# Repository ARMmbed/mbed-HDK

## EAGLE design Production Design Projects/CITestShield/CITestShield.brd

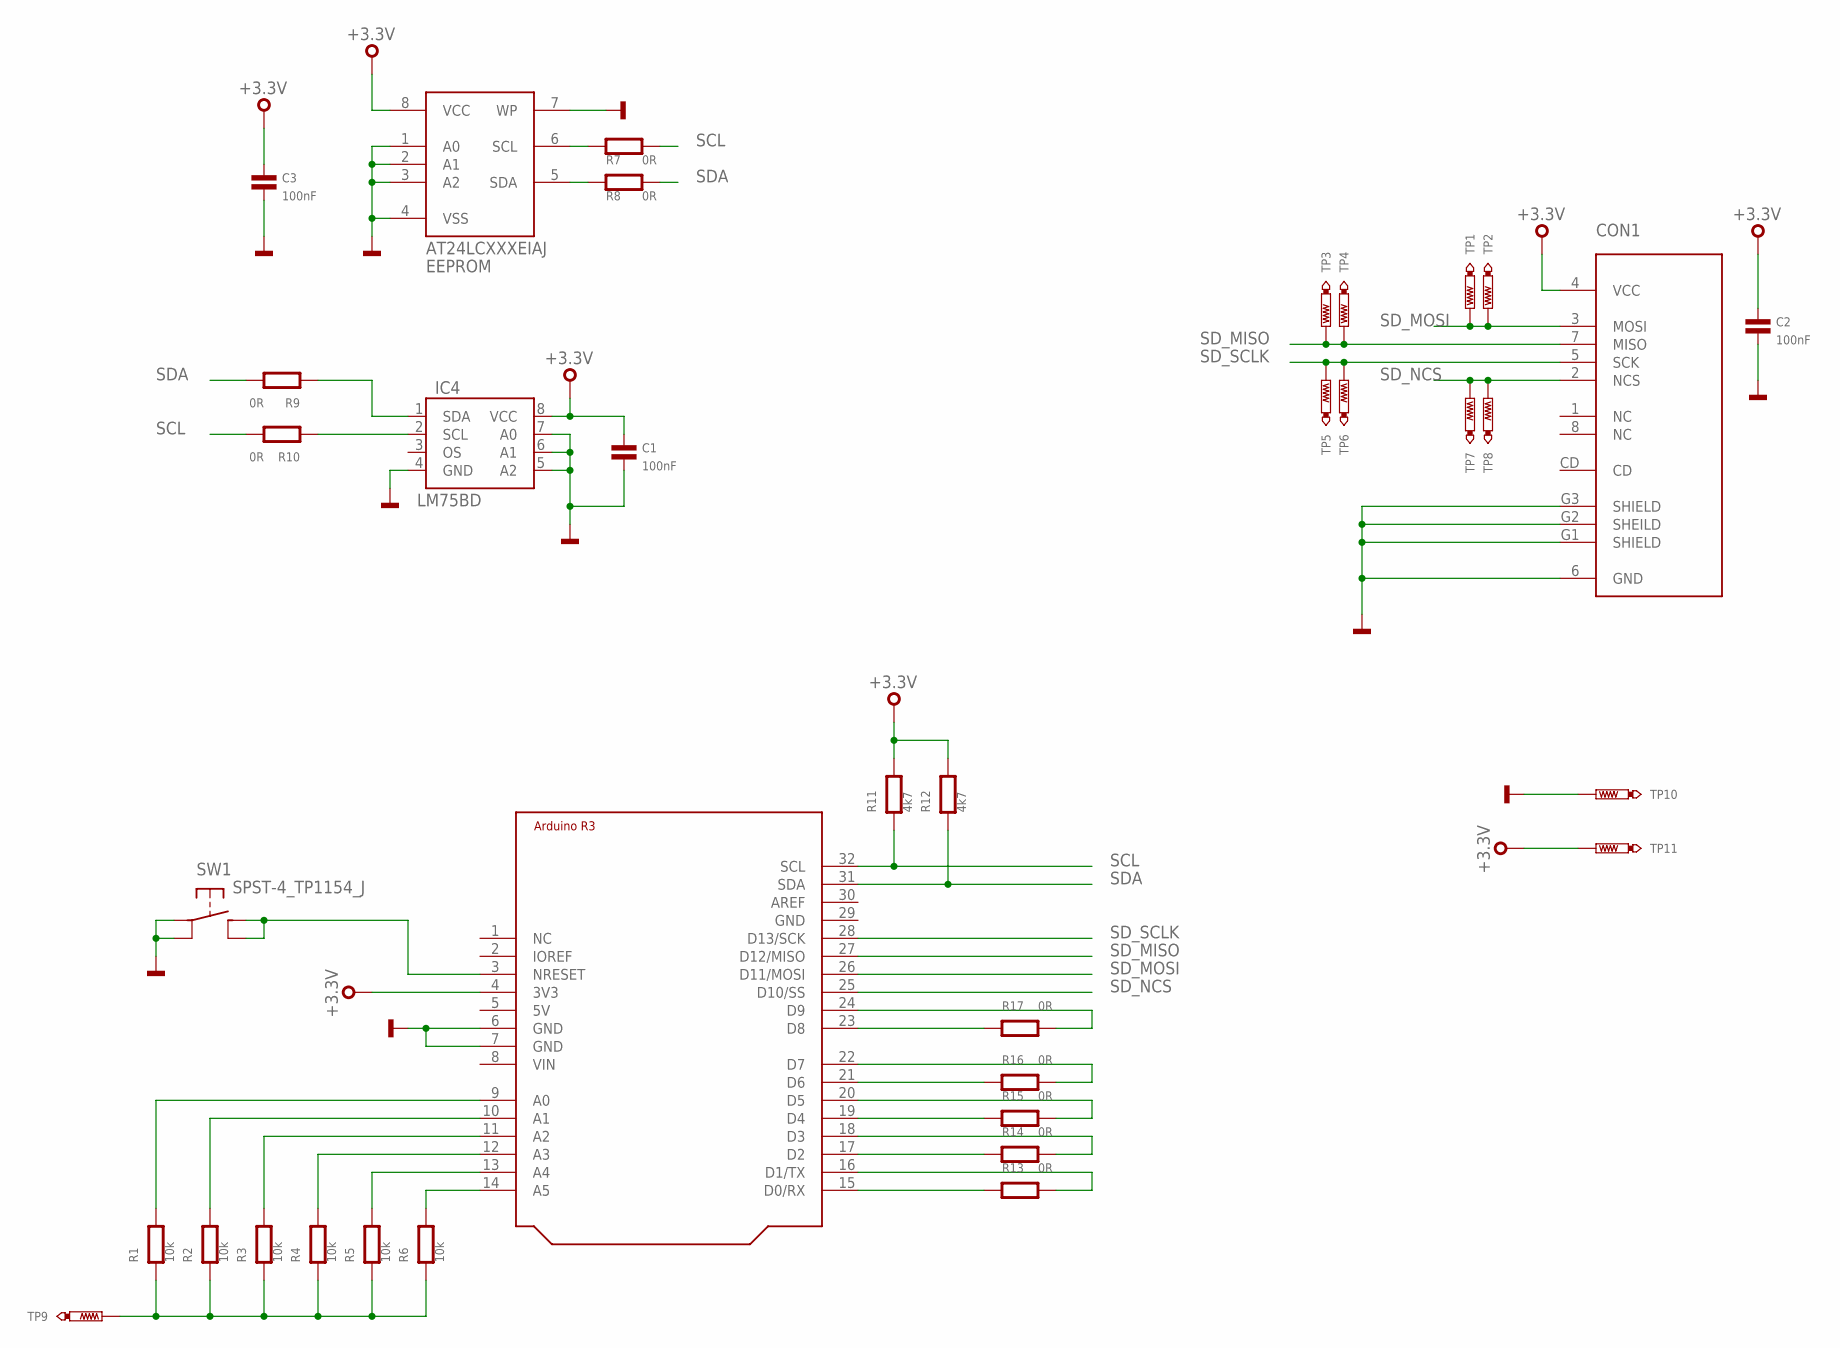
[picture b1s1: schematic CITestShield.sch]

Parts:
BRD1: ARDUINO-R3_SILK; ARDUINO-R3-SILK
C1, C2, C3: 100nF; 0603
CON1: MICRO-SD; AMPHENOL-101-00660-68-6
EEPROM: AT24LCXXXEIAJ; SO08-EIAJ
IC4: LM75BD; SO8
R1, R2, R3, R4, R5, R6: 10k; 0603
R7, R8, R9, R10, R13, R14, R15, R16, R17: 0R; 0603
R11, R12: 4k7; 0603
SW1: SPST-4_TP1154_J; TP-1154X
TP1, TP2, TP3, TP4, TP5, TP6, TP7, TP8, TP9, TP10, TP11: TEST-POINT-50R-SMD; TP50-SMD

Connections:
+3.3V: BRD1.4 (3V3), C1.1, C2.1, C3.1, CON1.4 (VCC), EEPROM.8 (VCC), IC4.8 (VCC), R11.2, R12.2, TP11.TP
GND: BRD1.6 (GND), BRD1.7 (GND), C1.2, C2.2, C3.2, CON1.6 (GND), CON1.G1 (SHIELD), CON1.G2 (SHEILD), CON1.G3 (SHIELD), EEPROM.1 (A0), EEPROM.2 (A1), EEPROM.3 (A2), EEPROM.4 (VSS), EEPROM.7 (WP), IC4.4 (GND), IC4.5 (A2), IC4.6 (A1), IC4.7 (A0), SW1.A1, SW1.A2, TP10.TP
unnamed: R1.1, R2.1, R3.1, R4.1, R5.1, R6.1, TP9.TP
unnamed: BRD1.9 (A0), R1.2
unnamed: BRD1.10 (A1), R2.2
unnamed: BRD1.11 (A2), R3.2
unnamed: BRD1.12 (A3), R4.2
unnamed: BRD1.13 (A4), R5.2
unnamed: BRD1.14 (A5), R6.2
unnamed: BRD1.21 (D6), R16.1
unnamed: BRD1.22 (D7), R16.2
unnamed: BRD1.24 (D9), R17.2
unnamed: BRD1.23 (D8), R17.1
unnamed: BRD1.16 (D1/TX), R13.2
unnamed: BRD1.15 (D0/RX), R13.1
unnamed: BRD1.17 (D2), R14.1
unnamed: BRD1.18 (D3), R14.2
unnamed: BRD1.20 (D5), R15.2
unnamed: BRD1.19 (D4), R15.1
unnamed: BRD1.3 (NRESET), SW1.B1, SW1.B2
unnamed: IC4.2 (SCL), R10.1
unnamed: IC4.1 (SDA), R9.1
unnamed: EEPROM.6 (SCL), R7.1
unnamed: EEPROM.5 (SDA), R8.1
SCL: BRD1.32 (SCL), R7.2, R10.2, R11.1
SDA: BRD1.31 (SDA), R8.2, R9.2, R12.1
SD_MISO: BRD1.27 (D12/MISO), CON1.7 (MISO), TP3.TP, TP4.TP
SD_MOSI: BRD1.26 (D11/MOSI), CON1.3 (MOSI), TP1.TP, TP2.TP
SD_NCS: BRD1.25 (D10/SS), CON1.2 (NCS), TP7.TP, TP8.TP
SD_SCLK: BRD1.28 (D13/SCK), CON1.5 (SCK), TP5.TP, TP6.TP

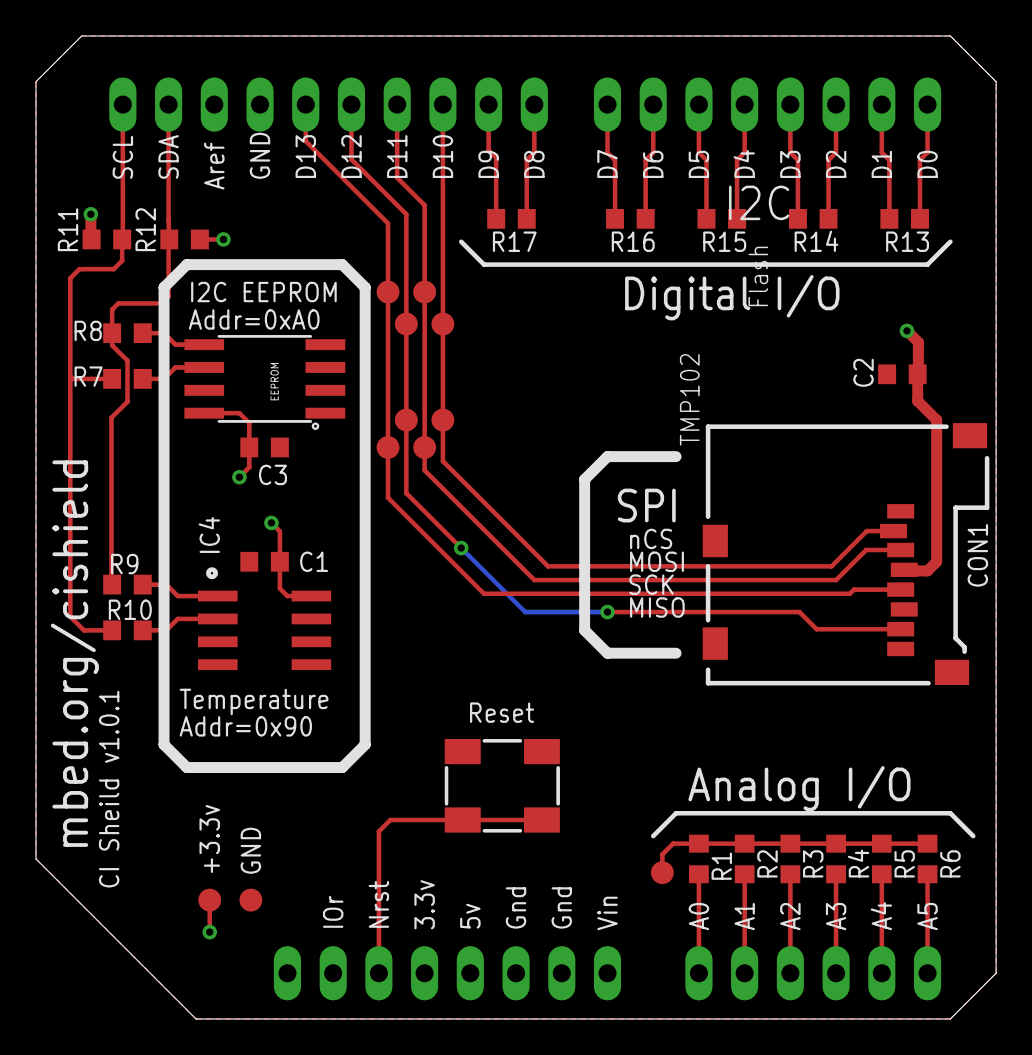
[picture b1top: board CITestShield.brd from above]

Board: 2 copper layers, 53.3 x 54.6 mm, 36 parts (0 on the bottom side), 30 nets.

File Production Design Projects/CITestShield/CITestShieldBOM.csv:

"Qty";"Value";"Device";"Package";"Parts";"Description";"";
"9";"0R";"R0603";"0603";"R7, R8, R9, R10, R13, R14, R15, R16, R17";"";"";
"3";"100nF";"C0603";"0603";"C1, C2, C3";"Capacitor";"";
"6";"10k";"R0603";"0603";"R1, R2, R3, R4, R5, R6";"";"";
"2";"4k7";"R0603";"0603";"R11, R12";"";"";
"1";"ARDUINO-R3_SILK";"ARDUINO-R3_SILK";"ARDUINO-R3-SILK";"BRD1";"";"";
"1";"AT24LCXXXEIAJ";"AT24LCXXXEIAJ";"SO08-EIAJ";"EEPROM";"I2C EEPROM, 24LC family";"";
"1";"LM75BD";"LM75BD";"SO8";"IC4";"";"";
"1";"MICRO-SD";"MICRO-SD";"AMPHENOL-101-00660-68-6";"CON1";"";"";
"1";"SPST-4_TP1154_J";"SPST-4_TP1154_J";"TP-1154X";"SW1";"";"";
"11";"TEST-POINT-50R-SMD";"TEST-POINT-50R-SMD";"TP50-SMD";"TP1, TP2, TP3, TP4, TP5, TP6, TP7, TP8, TP9, TP10, TP11";"";"";

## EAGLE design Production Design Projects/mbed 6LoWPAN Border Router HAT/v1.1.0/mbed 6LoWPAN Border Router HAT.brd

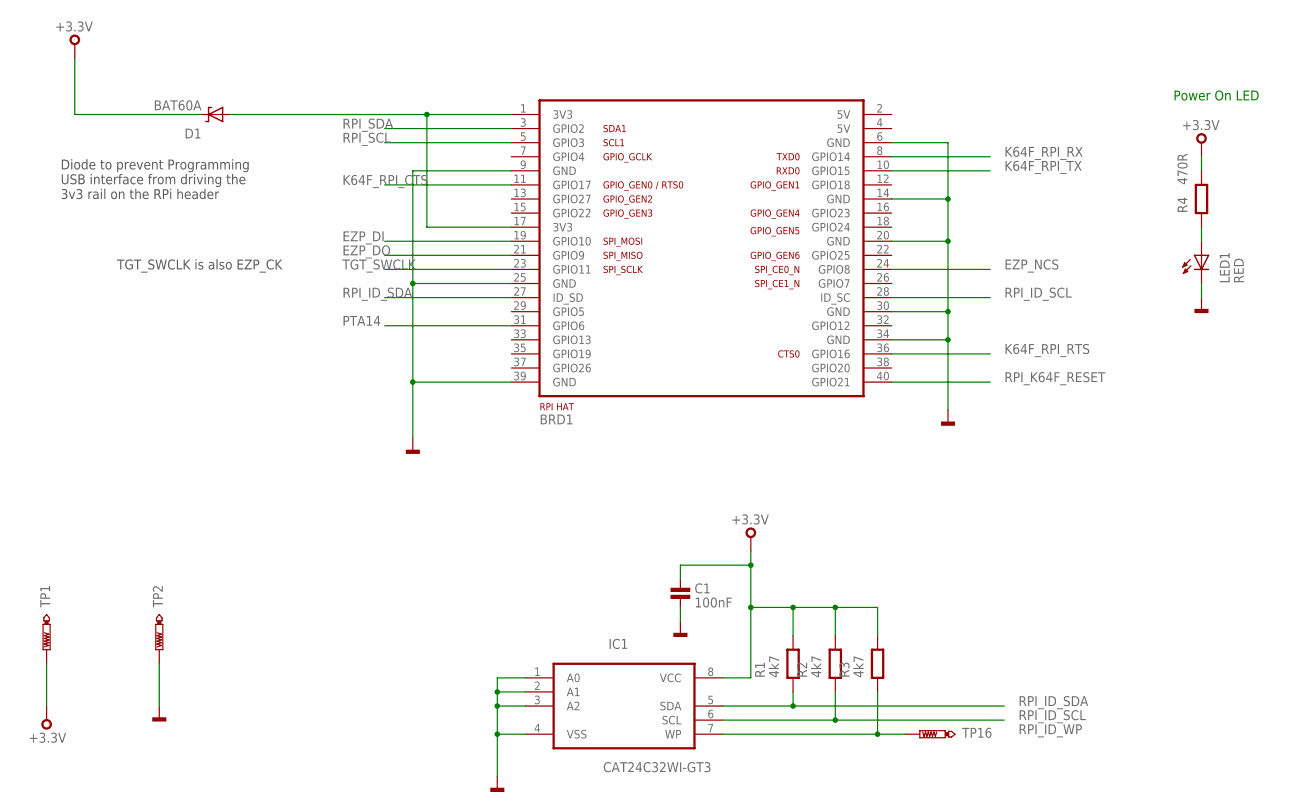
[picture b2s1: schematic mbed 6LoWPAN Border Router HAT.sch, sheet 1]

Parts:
BRD1: RPI-HAT
C1: 100nF; 0402
D1: BAT60A; SOD323
IC1: CAT24C32WI-GT3; SOIC127P600X175-8N
LED1: RED; CHIPLED_0603
R1, R2, R3: 4k7; 0402
R4: 470R; 0402
TP1, TP2, TP16: TEST-POINT-50R-PTH; TP50-PTH

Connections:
+3.3V: C1.1, D1.K, IC1.8 (VCC), R1.2, R2.2, R3.2, R4.2, TP1.TP; also elsewhere on the board
EZP_DI: BRD1.19 (GPIO10); also elsewhere on the board
EZP_DO: BRD1.21 (GPIO9); also elsewhere on the board
EZP_NCS: BRD1.24 (GPIO8); also elsewhere on the board
GND: BRD1.6 (GND), BRD1.9 (GND), BRD1.14 (GND), BRD1.20 (GND), BRD1.25 (GND), BRD1.30 (GND), BRD1.34 (GND), BRD1.39 (GND), C1.2, IC1.1 (A0), IC1.2 (A1), IC1.3 (A2), IC1.4 (VSS), LED1.C, TP2.TP; also elsewhere on the board
K64F_RPI_CTS: BRD1.11 (GPIO17); also elsewhere on the board
K64F_RPI_RTS: BRD1.36 (GPIO16); also elsewhere on the board
K64F_RPI_RX: BRD1.8 (GPIO14); also elsewhere on the board
K64F_RPI_TX: BRD1.10 (GPIO15); also elsewhere on the board
unnamed: BRD1.1 (3V3), BRD1.17 (3V3), D1.A
unnamed: LED1.A, R4.1
PTA14: BRD1.31 (GPIO6); also elsewhere on the board
RPI_ID_SCL: BRD1.28 (ID_SC), IC1.6 (SCL), R2.1
RPI_ID_SDA: BRD1.27 (ID_SD), IC1.5 (SDA), R1.1
RPI_ID_WP: IC1.7 (WP), R3.1, TP16.TP
RPI_K64F_RESET: BRD1.40 (GPIO21); also elsewhere on the board
RPI_SCL: BRD1.5 (GPIO3); also elsewhere on the board
RPI_SDA: BRD1.3 (GPIO2); also elsewhere on the board
TGT_SWCLK: BRD1.23 (GPIO11); also elsewhere on the board

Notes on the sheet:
Power On LED
Diode to prevent Programming USB interface from driving the 3v3 rail on the RPi header
TGT_SWCLK is also EZP_CK

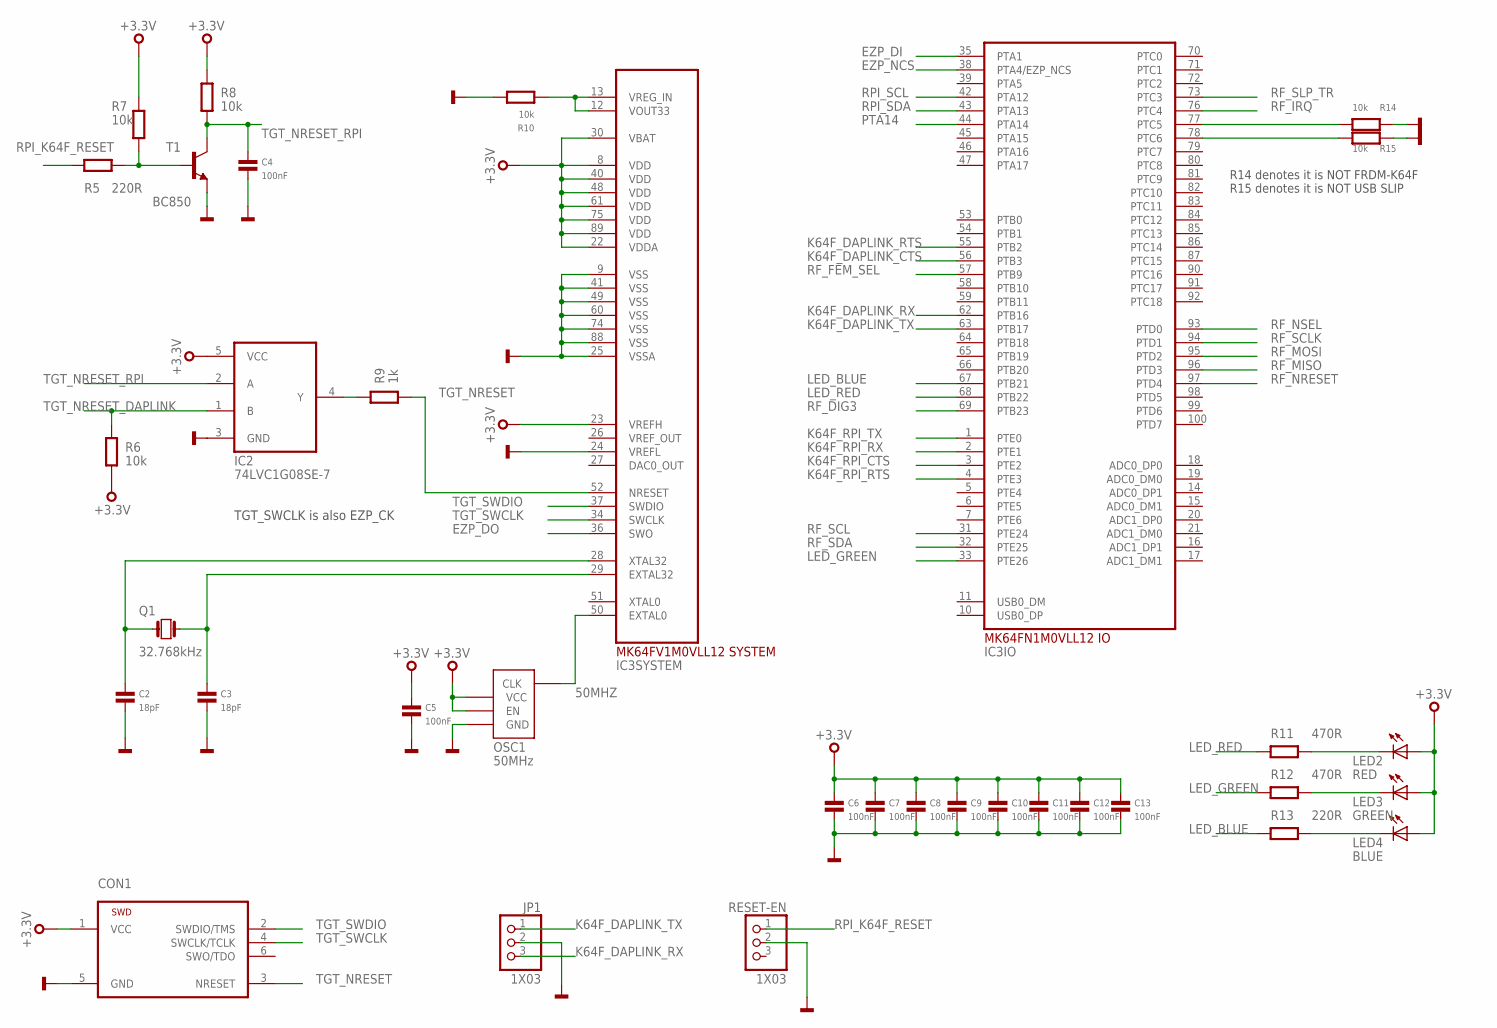
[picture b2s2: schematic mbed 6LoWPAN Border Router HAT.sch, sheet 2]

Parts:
C2, C3: 18pF; 0402
C4, C5, C6, C7, C8, C9, C10, C11, C12, C13: 100nF; 0402
CON1: TC2030-CTX-NL
IC2: 74LVC1G08SE-7; SOT353
IC3: MK64FN1M0VLL12; LQFP100
JP1: 1X03
LED2: RED; CHIPLED_0603
LED3: GREEN; CHIPLED_0603
LED4: BLUE; CHIPLED_0603
OSC1: 50MHz; 3.2X.2.5
Q1: 32.768kHz; FC135
R5, R13: 220R; 0402
R6, R7, R8, R10, R14, R15: 10k; 0402
R9: 1k; 0402
R11, R12: 470R; 0402
RESET-EN: 1X03
T1: BC850; SOT23

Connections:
50MHZ: IC3.50 (EXTAL0), OSC1.P$3 (CLK)
+3.3V: C5.1, C6.1, C7.1, C8.1, C9.1, C10.1, C11.1, C12.1, C13.1, CON1.1 (VCC), IC2.5 (VCC), IC3.8 (VDD), IC3.22 (VDDA), IC3.23 (VREFH), IC3.30 (VBAT), IC3.40 (VDD), IC3.48 (VDD), IC3.61 (VDD), IC3.75 (VDD), IC3.89 (VDD), LED2.A, LED3.A, LED4.A, OSC1.P$1 (EN), OSC1.P$4 (VCC), R6.1, R7.1, R8.2; also elsewhere on the board
EZP_DI: IC3.35 (PTA1); also elsewhere on the board
EZP_DO: IC3.36 (SWO); also elsewhere on the board
EZP_NCS: IC3.38 (PTA4/EZP_NCS); also elsewhere on the board
GND: C2.2, C3.2, C4.2, C5.2, C6.2, C7.2, C8.2, C9.2, C10.2, C11.2, C12.2, C13.2, CON1.5 (GND), IC2.3 (GND), IC3.9 (VSS), IC3.24 (VREFL), IC3.25 (VSSA), IC3.41 (VSS), IC3.49 (VSS), IC3.60 (VSS), IC3.74 (VSS), IC3.88 (VSS), JP1.2, OSC1.P$2 (GND), R10.2, R14.2, R15.2, RESET-EN.2, T1.2 (E); also elsewhere on the board
K64F_DAPLINK_CTS: IC3.56 (PTB3); also elsewhere on the board
K64F_DAPLINK_RTS: IC3.55 (PTB2); also elsewhere on the board
K64F_DAPLINK_RX: IC3.62 (PTB16), JP1.3; also elsewhere on the board
K64F_DAPLINK_TX: IC3.63 (PTB17), JP1.1; also elsewhere on the board
K64F_RPI_CTS: IC3.3 (PTE2); also elsewhere on the board
K64F_RPI_RTS: IC3.4 (PTE3); also elsewhere on the board
K64F_RPI_RX: IC3.2 (PTE1); also elsewhere on the board
K64F_RPI_TX: IC3.1 (PTE0); also elsewhere on the board
LED_BLUE: IC3.67 (PTB21), R13.1
LED_GREEN: IC3.33 (PTE26), R12.1
LED_RED: IC3.68 (PTB22), R11.1
unnamed: C2.1, IC3.28 (XTAL32), Q1.X1 (1)
unnamed: C3.1, IC3.29 (EXTAL32), Q1.X2 (2)
unnamed: IC3.77 (PTC5), R14.1
unnamed: IC3.12 (VOUT33), IC3.13 (VREG_IN), R10.1
unnamed: LED2.C, R11.2
unnamed: LED3.C, R12.2
unnamed: LED4.C, R13.2
unnamed: R5.1, R7.2, T1.1 (B)
unnamed: IC2.4 (Y), R9.2
unnamed: IC3.78 (PTC6), R15.1
PTA14: IC3.44 (PTA14); also elsewhere on the board
RF_DIG3: IC3.69 (PTB23); also elsewhere on the board
RF_FEM_SEL: IC3.57 (PTB9); also elsewhere on the board
RF_IRQ: IC3.76 (PTC4); also elsewhere on the board
RF_MISO: IC3.96 (PTD3); also elsewhere on the board
RF_MOSI: IC3.95 (PTD2); also elsewhere on the board
RF_NRESET: IC3.97 (PTD4); also elsewhere on the board
RF_NSEL: IC3.93 (PTD0); also elsewhere on the board
RF_SCL: IC3.31 (PTE24); also elsewhere on the board
RF_SCLK: IC3.94 (PTD1); also elsewhere on the board
RF_SDA: IC3.32 (PTE25); also elsewhere on the board
RF_SLP_TR: IC3.73 (PTC3); also elsewhere on the board
RPI_K64F_RESET: R5.2, RESET-EN.1; also elsewhere on the board
RPI_SCL: IC3.42 (PTA12); also elsewhere on the board
RPI_SDA: IC3.43 (PTA13); also elsewhere on the board
TGT_NRESET: CON1.3 (NRESET), IC3.52 (NRESET), R9.1; also elsewhere on the board
TGT_NRESET_DAPLINK: IC2.1 (B), R6.2; also elsewhere on the board
TGT_NRESET_RPI: C4.1, IC2.2 (A), R8.1, T1.3 (C)
TGT_SWCLK: CON1.4 (SWCLK/TCLK), IC3.34 (SWCLK); also elsewhere on the board
TGT_SWDIO: CON1.2 (SWDIO/TMS), IC3.37 (SWDIO); also elsewhere on the board

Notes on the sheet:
TGT_SWCLK is also EZP_CK
R14 denotes it is NOT FRDM-K64F R15 denotes it is NOT USB SLIP

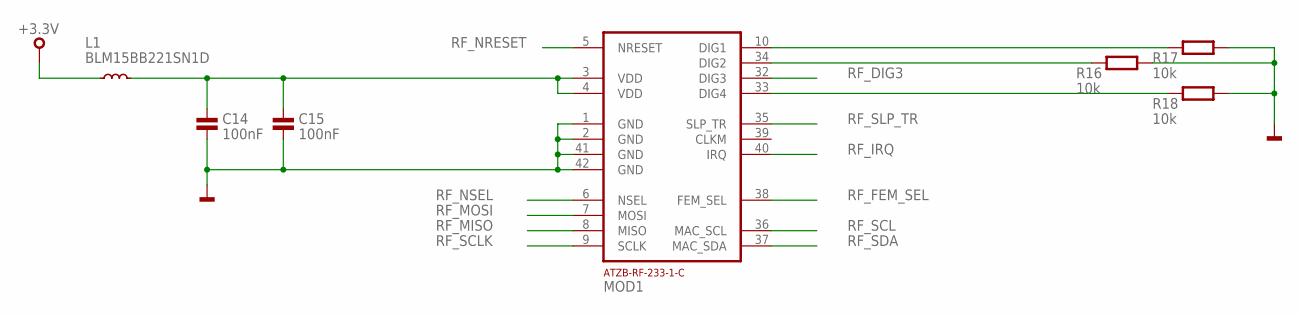
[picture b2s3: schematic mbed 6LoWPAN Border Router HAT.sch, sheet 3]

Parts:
C14, C15: 100nF; 0402
L1: BLM15BB221SN1D; 0402
MOD1: ATZB-RF-233-1-C
R16, R17, R18: 10k; 0402

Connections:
+3.3V: L1.1; also elsewhere on the board
GND: C14.2, C15.2, MOD1.1 (GND), MOD1.2 (GND), MOD1.41 (GND), MOD1.42 (GND), R16.2, R17.2, R18.1; also elsewhere on the board
unnamed: MOD1.10 (DIG1), R17.1
unnamed: MOD1.34 (DIG2), R16.1
unnamed: MOD1.33 (DIG4), R18.2
unnamed: C14.1, C15.1, L1.2, MOD1.3 (VDD), MOD1.4 (VDD)
RF_DIG3: MOD1.32 (DIG3); also elsewhere on the board
RF_FEM_SEL: MOD1.38 (FEM_SEL); also elsewhere on the board
RF_IRQ: MOD1.40 (IRQ); also elsewhere on the board
RF_MISO: MOD1.8 (MISO); also elsewhere on the board
RF_MOSI: MOD1.7 (MOSI); also elsewhere on the board
RF_NRESET: MOD1.5 (NRESET); also elsewhere on the board
RF_NSEL: MOD1.6 (NSEL); also elsewhere on the board
RF_SCL: MOD1.36 (MAC_SCL); also elsewhere on the board
RF_SCLK: MOD1.9 (SCLK); also elsewhere on the board
RF_SDA: MOD1.37 (MAC_SDA); also elsewhere on the board
RF_SLP_TR: MOD1.35 (SLP_TR); also elsewhere on the board

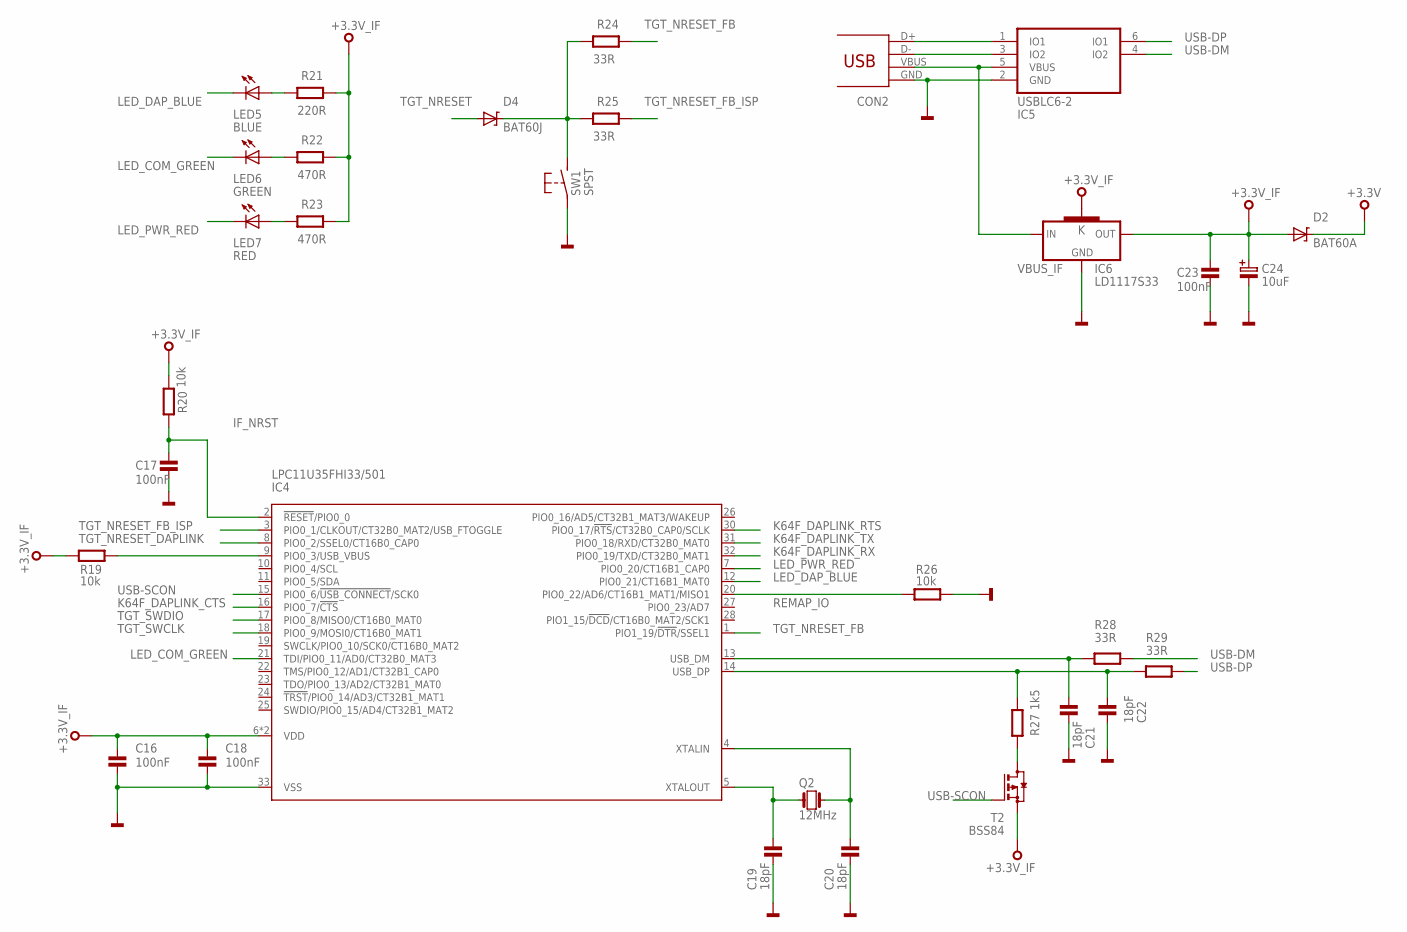
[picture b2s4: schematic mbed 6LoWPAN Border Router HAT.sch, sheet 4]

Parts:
C16, C17, C18, C23: 100nF; 0402
C19, C20, C21, C22: 18pF; 0402
C24: 10uF; SMC_B
CON2: USB_MICROB; MOLEX-47364-0001
D2: BAT60A; SOD323
D4: BAT60J; SOD323
IC4: LPC11U35FHI33/501; SOT617-3
IC5: USBLC6-2SC6; SOT23-6L
IC6: LD1117S33; SOT223
LED5: BLUE; CHIPLED_0603
LED6: GREEN; CHIPLED_0603
LED7: RED; CHIPLED_0603
Q2: 12MHz; 3.2X.2.5
R19, R20, R26: 10k; 0402
R21: 220R; 0402
R22, R23: 470R; 0402
R24, R25, R28, R29: 33R; 0402
R27: 1k5; 0402
SW1: SPST; DTSM-32S-B
T2: BSS84; SOT23

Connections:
+3.3V: D2.K; also elsewhere on the board
+3.3V_IF: C16.1, C18.1, C23.1, C24.+, D2.A, IC4.6 (VDD), IC4.29 (VDD), IC6.2 (OUT), IC6.4 (K), R19.2, R20.2, R21.1, R22.1, R23.1, T2.2 (S)
D+: CON2.D+, IC5.1 (IO1)
D-: CON2.D-, IC5.3 (IO2)
DM: C21.1, IC4.13 (USB_DM), R28.2
DP: C22.1, IC4.14 (USB_DP), R27.2, R29.2
GND: C16.2, C17.2, C18.2, C19.2, C20.2, C21.2, C22.2, C23.2, C24.-, CON2.GND, IC4.33 (VSS), IC5.2 (GND), IC6.1 (GND), R26.1, SW1.P$1; also elsewhere on the board
IF_NRST: C17.1, IC4.2 (!RESET!/PIO0_0), R20.1
K64F_DAPLINK_CTS: IC4.16 (PIO0_7/!CTS!); also elsewhere on the board
K64F_DAPLINK_RTS: IC4.30 (PIO0_17/!RTS!/CT32B0_CAP0/SCLK); also elsewhere on the board
K64F_DAPLINK_RX: IC4.32 (PIO0_19/TXD/CT32B0_MAT1); also elsewhere on the board
K64F_DAPLINK_TX: IC4.31 (PIO0_18/RXD/CT32B0_MAT0); also elsewhere on the board
LED_COM_GREEN: IC4.21 (TDI/PIO0_11/AD0/CT32B0_MAT3), LED6.C
LED_DAP_BLUE: IC4.12 (PIO0_21/CT16B1_MAT0), LED5.C
LED_PWR_RED: IC4.7 (PIO0_20/CT16B1_CAP0), LED7.C
unnamed: D4.K, R24.2, R25.2, SW1.P$2 (S)
unnamed: C19.1, IC4.5 (XTALOUT), Q2.P$1 (1)
unnamed: C20.1, IC4.4 (XTALIN), Q2.P$3 (2)
unnamed: IC4.9 (PIO0_3/USB_VBUS), R19.1
unnamed: R27.1, T2.3 (D)
unnamed: LED6.A, R22.2
unnamed: LED7.A, R23.2
unnamed: LED5.A, R21.2
REMAP_IO: IC4.20 (PIO0_22/AD6/CT16B1_MAT1/MISO1), R26.2
TGT_NRESET: D4.A; also elsewhere on the board
TGT_NRESET_DAPLINK: IC4.8 (PIO0_2/SSEL0/CT16B0_CAP0); also elsewhere on the board
TGT_NRESET_FB: IC4.1 (PIO1_19/!DTR!/SSEL1), R24.1
TGT_NRESET_FB_ISP: IC4.3 (PIO0_1/CLKOUT/CT32B0_MAT2/USB_FTOGGLE), R25.1
TGT_SWCLK: IC4.18 (PIO0_9/MOSI0/CT16B0_MAT1); also elsewhere on the board
TGT_SWDIO: IC4.17 (PIO0_8/MISO0/CT16B0_MAT0); also elsewhere on the board
USB-DM: IC5.4 (IO2), R28.1
USB-DP: IC5.6 (IO1), R29.1
USB-SCON: IC4.15 (PIO0_6/!USB_CONNECT!/SCK0), T2.1 (G)
VBUS_IF: CON2.VBUS, IC5.5 (VBUS), IC6.3 (IN)

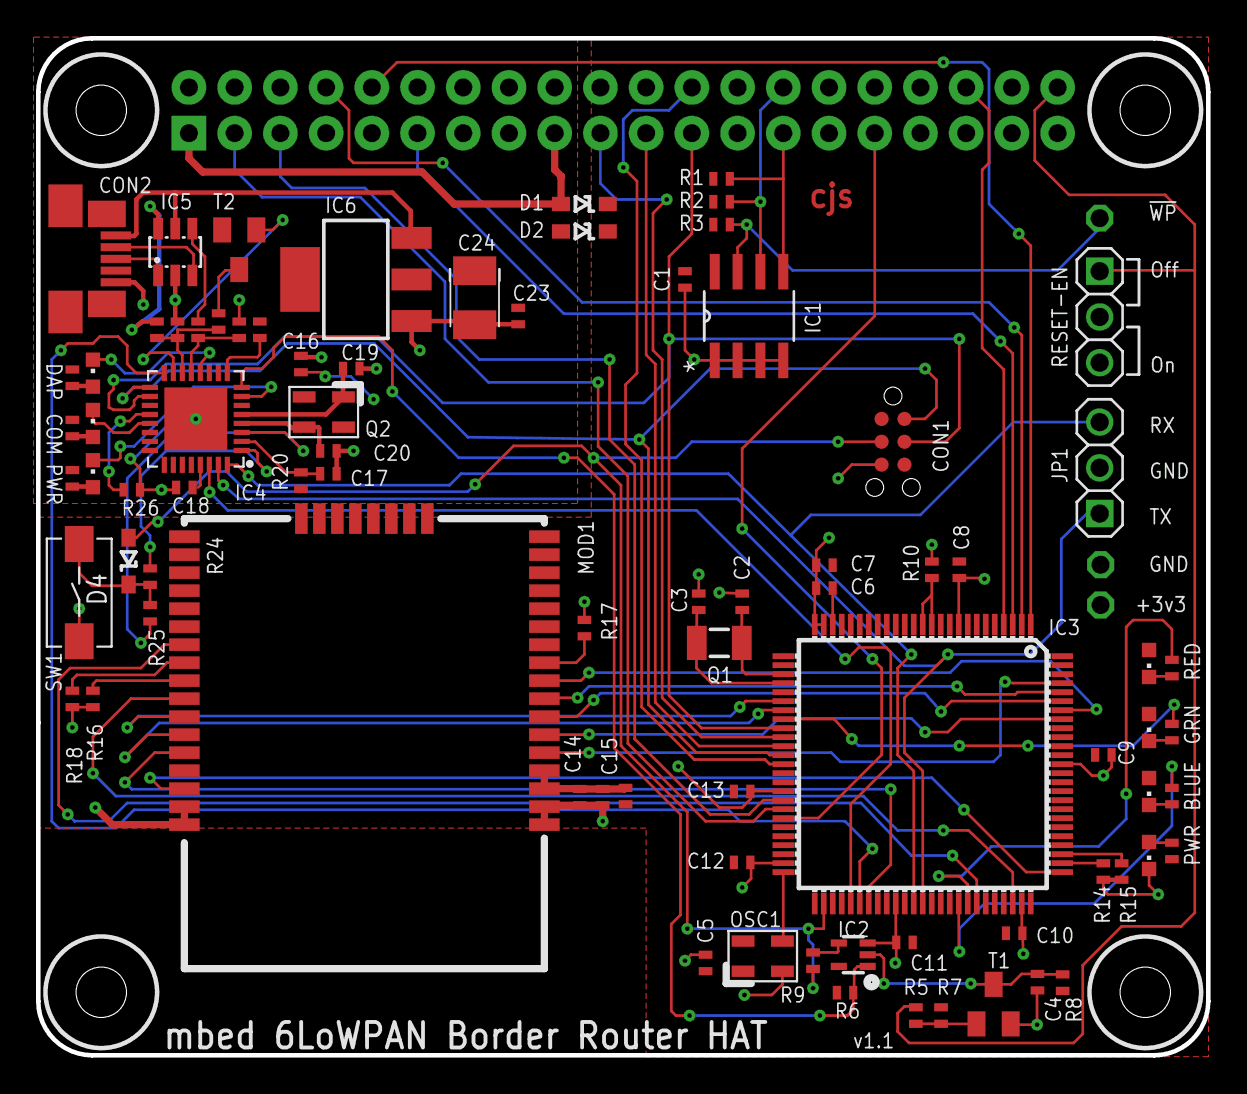
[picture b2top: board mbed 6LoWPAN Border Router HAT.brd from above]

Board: 2 copper layers, 65.0 x 56.5 mm, 85 parts (0 on the bottom side), 80 nets.

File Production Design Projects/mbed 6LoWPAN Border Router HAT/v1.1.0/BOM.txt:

Qty Value              Device             Package            Parts                                                                        Description                                                   
17  100nF              C0402              0402               C1, C4, C5, C6, C7, C8, C9, C10, C11, C12, C13, C14, C15, C16, C17, C18, C23 Capacitor                                                     
12  10k                R0402              0402               R6, R7, R8, R10, R14, R15, R16, R17, R18, R19, R20, R26                                                                                    
1   10uF               C-POLB             CASE B              C24                                                                          Polarised capacitor                                           
1   12MHz              Q_3.2X2.5          3.2X.2.5           Q2                                                                                                                                         
6   18pF               C0402              0402               C2, C3, C19, C20, C21, C22                                                   Capacitor                                                     
2   1X03               PINHD-1X3          1X03               JP1, RESET-EN                                                                PIN HEADER                                                    
1   1k                 R0402              0402               R9                                                                                                                                         
1   1k5                R0402              0402               R27                                                                                                                                        
3   220R               R0402              0402               R5, R13, R21                                                                                                                               
1   32.768kHz          Q_FC135            FC135              Q1                                                                                                                                         
4   33R                R0402              0402               R24, R25, R28, R29                                                                                                                         
5   470R               R0402              0402               R4, R11, R12, R22, R23                                                                                                                     
3   4k7                R0402              0402               R1, R2, R3                                                                                                                                 
1   50MHz              OSCILLATOR3.2X2.5  3.2X.2.5           OSC1                                                                                                                                       
1   74LVC1G08SE-7      74LVC1GXX          SOT353             IC2                                                                                                                                        
1   ATZB-RF-233-1-CR   ATZB-RF-233-1-CR   ATZB-RF-233-1-CR   MOD1                                                                                                                                       
2   BAT60A             BAT60A             BAT60A             D1, D2                                                                       Schottky Diode                                                
1   BAT60J             BAT60J             BAT60J             D3                                                                           Schottky Diode                                                
1   BC850              BC850              SOT23              T1                                                                           NPN TRANSISTOR                                                
1   BLM15BB221SN1D     L0402              0402               L1                                                                           Inductor                                                      
2   BLUE               LED0603            CHIPLED_0603       LED4, LED5                                                                   SMD LED                                                       
1   BSS84              BSS84              SOT23              T2                                                                           P-CHANNEL MOS FET                                             
1   CAT24C32WI-GT3     CAT24C32WI-GT3     SOIC127P600X175-8N IC1                                                                          32-Kb I2C CMOS Serial  EEPROM                                 
2   GREEN              LED0603            CHIPLED_0603       LED3, LED6                                                                   SMD LED                                                       
1   LD1117S33CTR       LD1117S33CTR       SOT223             IC6                                                                          VOLTAGE REGULATOR SMD 3,3V                                    
1   LPC11U35FHI33/501  LPC11U35FHI33/501  SOT617-3           IC4                                                                          32-bit ARM Cortex-M0 microcontroller; up to 128  kB flash; up 
1   MK64FN1M0VLL12     MK64FN1M0VLL12     LQFP100            IC3                                                                                                                                        
3   RED                LED0603            CHIPLED_0603       LED1, LED2, LED7                                                             SMD LED                                                       
1   RPI-HAT            2X20PIN 2.54mm     M20-7831046        BRD                                                                                                                                   
1   SPST               SPST               DTSM-32S-B         SW1                                                                                                                                                                                                                                                                    
1   USBLC6-2SC6        USBLC6-2SC6        SOT23-6L           IC5                                                                                                                                        
1   USB_MICROB         USB_MICROB         MOLEX-47346-0001   CON2                                                                         USB Connectors
